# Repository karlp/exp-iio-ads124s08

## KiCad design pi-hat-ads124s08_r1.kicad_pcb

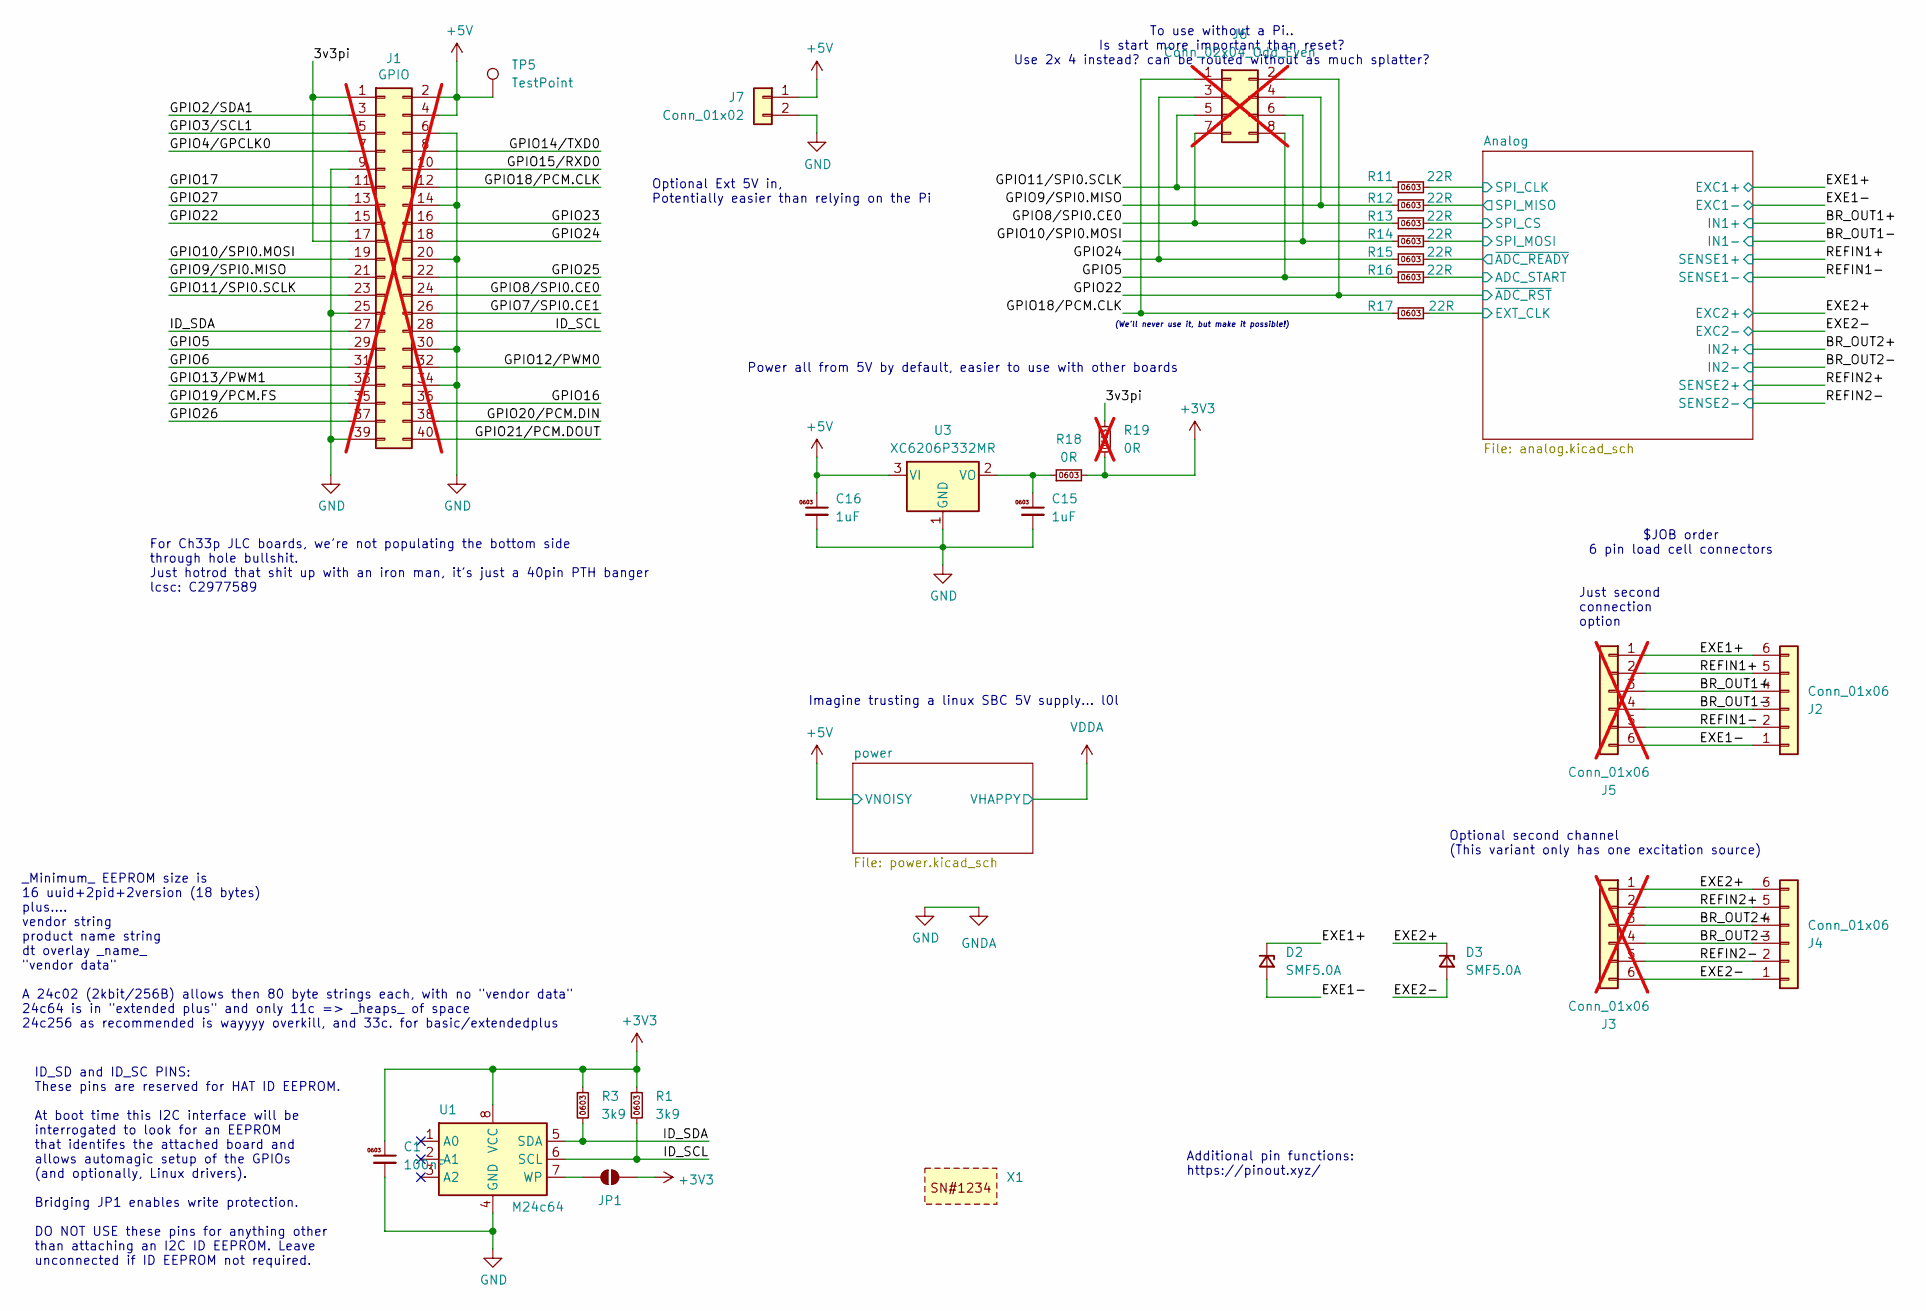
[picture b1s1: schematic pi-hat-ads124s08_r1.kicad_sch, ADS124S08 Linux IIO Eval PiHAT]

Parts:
C1: 100nF; C_0603_1608Metric; MPN CC0603KRX7R9BB104; LCSC Part # C14663
C15, C16: 1uF; C_0603_1608Metric; MPN CL10A105KB8NNNC; LCSC Part # C15849
D2, D3: SMF5.0A; D_SOD-123F; MPN SMF5.0A; LCSC Part # C19077497
J1: GPIO; PinSocket_2x20_P2.54mm_Vertical; not fitted
J2, J4: Conn_01x06; PhoenixContact_MCV_1,5_6-G-3.81_1x06_P3.81mm_Vertical; MPN KF2EDGV-3.81-6P; LCSC Part # C441336
J3, J5: Conn_01x06; PinHeader_1x06_P2.54mm_Vertical; not fitted
J6: Conn_02x04_Odd_Even; PinHeader_2x04_P2.54mm_Vertical; not fitted
J7: Conn_01x02; PhoenixContact_MCV_1,5_2-G-3.81_1x02_P3.81mm_Vertical; MPN WJ15EDGVC-3.81-2P; LCSC Part # C8396
JP1: ID_WP; SolderJumper-2_P1.3mm_Open_TrianglePad0.9x1.8mm
R1, R3: 3k9; R_0603_1608Metric; MPN 0603WAF3901T5E; LCSC Part # C23018
R11, R12, R13, R14, R15, R16, R17: 22R; R_0603_1608Metric; MPN 0603WAF220JT5E; LCSC Part # C23345
R18: 0R; R_0603_1608Metric; MPN 0603WAF0000T5E; LCSC Part # C21189
R19: 0R; R_0603_1608Metric; MPN 0603WAF0000T5E; LCSC Part # C21189; not fitted
TP5: TestPoint; TestPoint_THTPad_2.0x2.0mm_Drill1.0mm
U1: M24c64; SOIC-8_3.9x4.9mm_P1.27mm; MPN M24C64-RMN6TP; LCSC Part # C79988
U3: XC6206P332MR; SOT-23-3; MPN XC6206P332MR-G; LCSC Part # C5446
X1: JLC_2D_BARCODE_8x8mm

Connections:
+3V3: C1.1, JP1.2 (B), R1.1, R3.1, R18.2, R19.1, U1.8 (VCC); also elsewhere on the board
+5V: C16.1, J1.2, J1.4, J7.1, TP5.1, U3.3 (VI); also elsewhere on the board
/3v3pi: J1.1, J1.17, R19.2
/Analog/ADC_START: R16.2; also elsewhere on the board
/Analog/EXT_CLK: R17.2; also elsewhere on the board
/Analog/SPI_CLK: R11.2; also elsewhere on the board
/Analog/SPI_CS: R13.2; also elsewhere on the board
/Analog/SPI_MISO: R12.2; also elsewhere on the board
/Analog/SPI_MOSI: R14.2; also elsewhere on the board
/Analog/~ADC_READY: R15.2; also elsewhere on the board
/BR_OUT1+: J2.4, J5.3; also elsewhere on the board
/BR_OUT1-: J2.3, J5.4; also elsewhere on the board
/BR_OUT2+: J3.3, J4.4; also elsewhere on the board
/BR_OUT2-: J3.4, J4.3; also elsewhere on the board
/EXE1+: D2.1 (K), D3.1 (K), J2.6, J3.1, J4.6, J5.1; also elsewhere on the board
/GPIO2/SDA1: J1.3
/GPIO3/SCL1: J1.5
/GPIO4/GPCLK0: J1.7
/GPIO5: J1.29, J6.8, R16.1
/GPIO6: J1.31
/GPIO7/SPI0.CE1: J1.26
/GPIO8/SPI0.CE0: J1.24, J6.7, R13.1
/GPIO9/SPI0.MISO: J1.21, J6.4, R12.1
/GPIO10/SPI0.MOSI: J1.19, J6.6, R14.1
/GPIO11/SPI0.SCLK: J1.23, J6.5, R11.1
/GPIO12/PWM0: J1.32
/GPIO13/PWM1: J1.33
/GPIO14/TXD0: J1.8
/GPIO15/RXD0: J1.10
/GPIO16: J1.36
/GPIO17: J1.11
/GPIO18/PCM.CLK: J1.12, J6.1, R17.1
/GPIO19/PCM.FS: J1.35
/GPIO20/PCM.DIN: J1.38
/GPIO21/PCM.DOUT: J1.40
/GPIO22: J1.15, J6.2; also elsewhere on the board
/GPIO23: J1.16
/GPIO24: J1.18, J6.3, R15.1
/GPIO25: J1.22
/GPIO26: J1.37
/GPIO27: J1.13
/ID_SCL: J1.28, R1.2, U1.6 (SCL)
/ID_SDA: J1.27, R3.2, U1.5 (SDA)
/REFIN1+: J2.5, J5.2; also elsewhere on the board
/REFIN1-: J2.2, J5.5; also elsewhere on the board
/REFIN2+: J3.2, J4.5; also elsewhere on the board
/REFIN2-: J3.5, J4.2; also elsewhere on the board
GND: C1.2, C15.2, C16.2, D2.2 (A), D3.2 (A), J1.6, J1.9, J1.14, J1.20, J1.25, J1.30, J1.34, J1.39, J2.1, J3.6, J4.1, J5.6, J7.2, U1.4 (GND), U3.1 (GND); also elsewhere on the board
unnamed: JP1.1 (A), U1.7 (WP)
unnamed: C15.1, R18.1, U3.2 (VO)

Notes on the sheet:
Optional Ext 5V in, Potentially easier than relying on the Pi
Just second connection option
_Minimum_ EEPROM size is 16 uuid+2pid+2version (18 bytes) plus.... vendor string product name string dt overlay _name_ "vendor data" A 24c02 (2kbit/256B) allows then 80 byte strings each, with no "vendor data" 24c64 is in "extended plus" and only 11c => _heaps_ of space 24c256 as recommended is way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
To use without a Pi.. Is start more important than reset? Use 2x 4 instead? can be routed without as much splatter?
Additional pin functions: https://pinout.xyz/
$JOB order 6 pin load cell connectors
Power all from 5V by default, easier to use with other boards
ID_SD and ID_SC PINS: These pins are reserved for HAT ID EEPROM. At boot time this I2C interface will be interrogated to look for an EEPROM that identifes the attached board and allows automagic setup of the GPIOs (and optionally, Linux drivers). Bridging JP1 enables write protection. DO NOT USE th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
Optional second channel (This variant only has one excitation source)
For Ch33p JLC boards, we're not populating the bottom side through hole bullshit. Just hotrod that shit up with an iron man, it's just a 40pin PTH banger lcsc: C2977589
(We'll never use it, but make it possible!)
Imagine trusting a linux SBC 5V supply... l0l

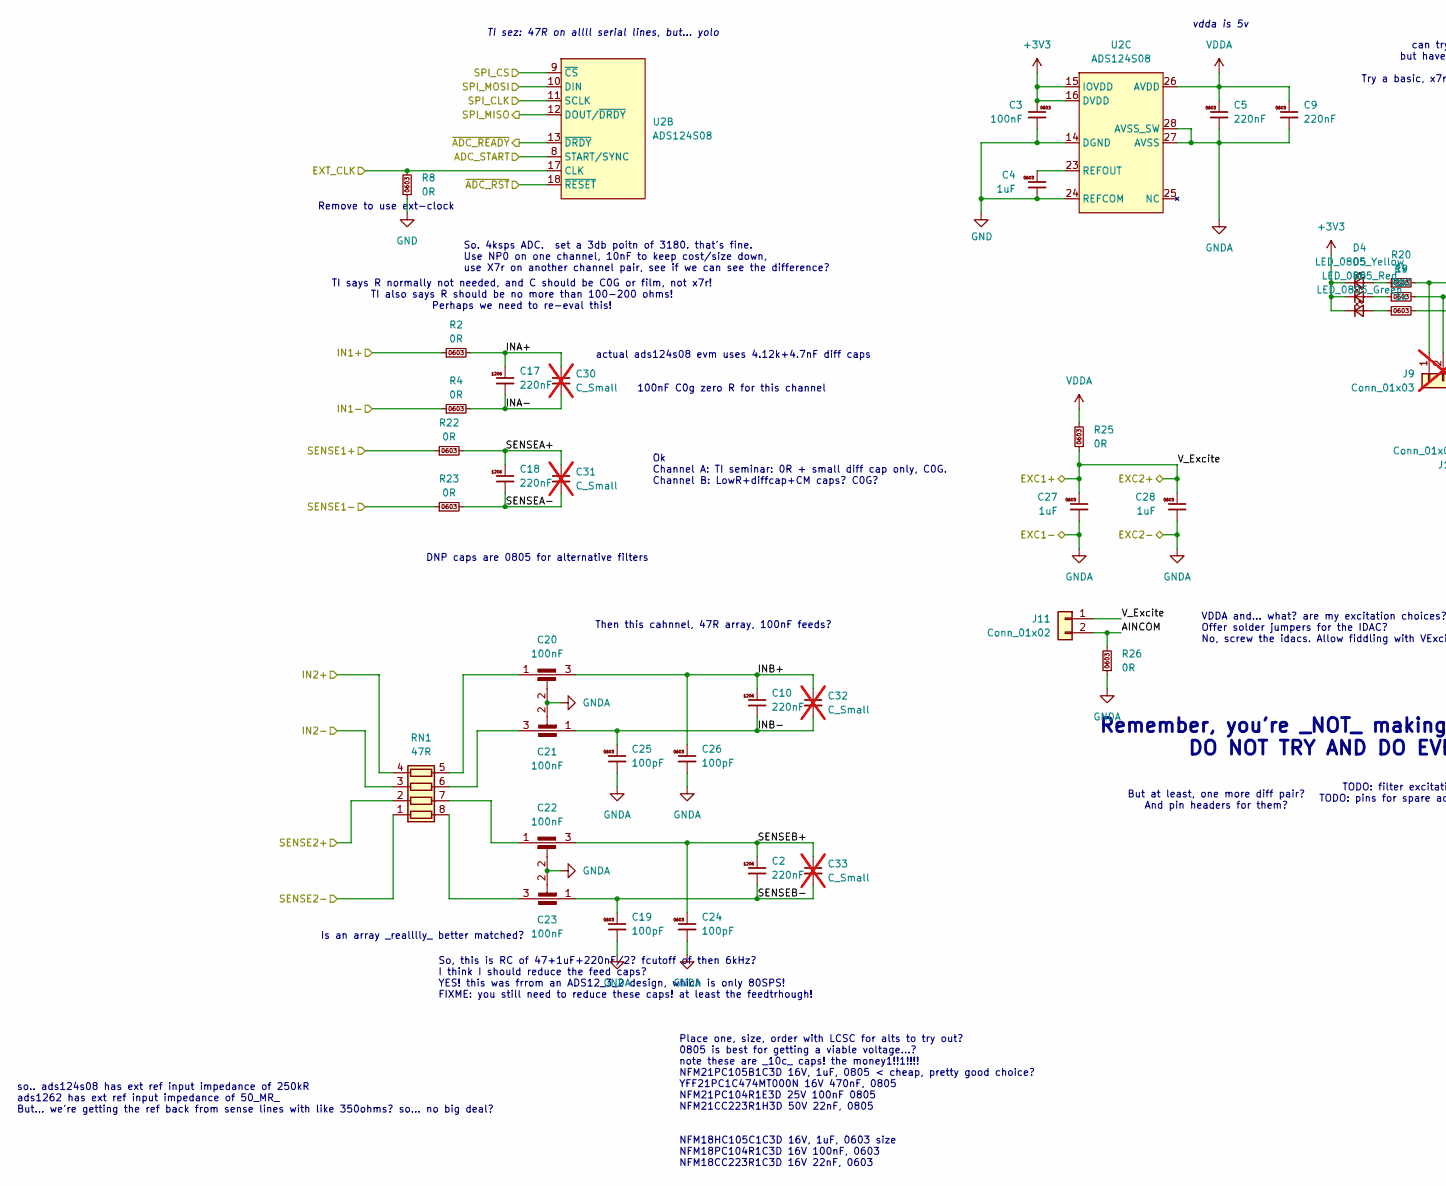
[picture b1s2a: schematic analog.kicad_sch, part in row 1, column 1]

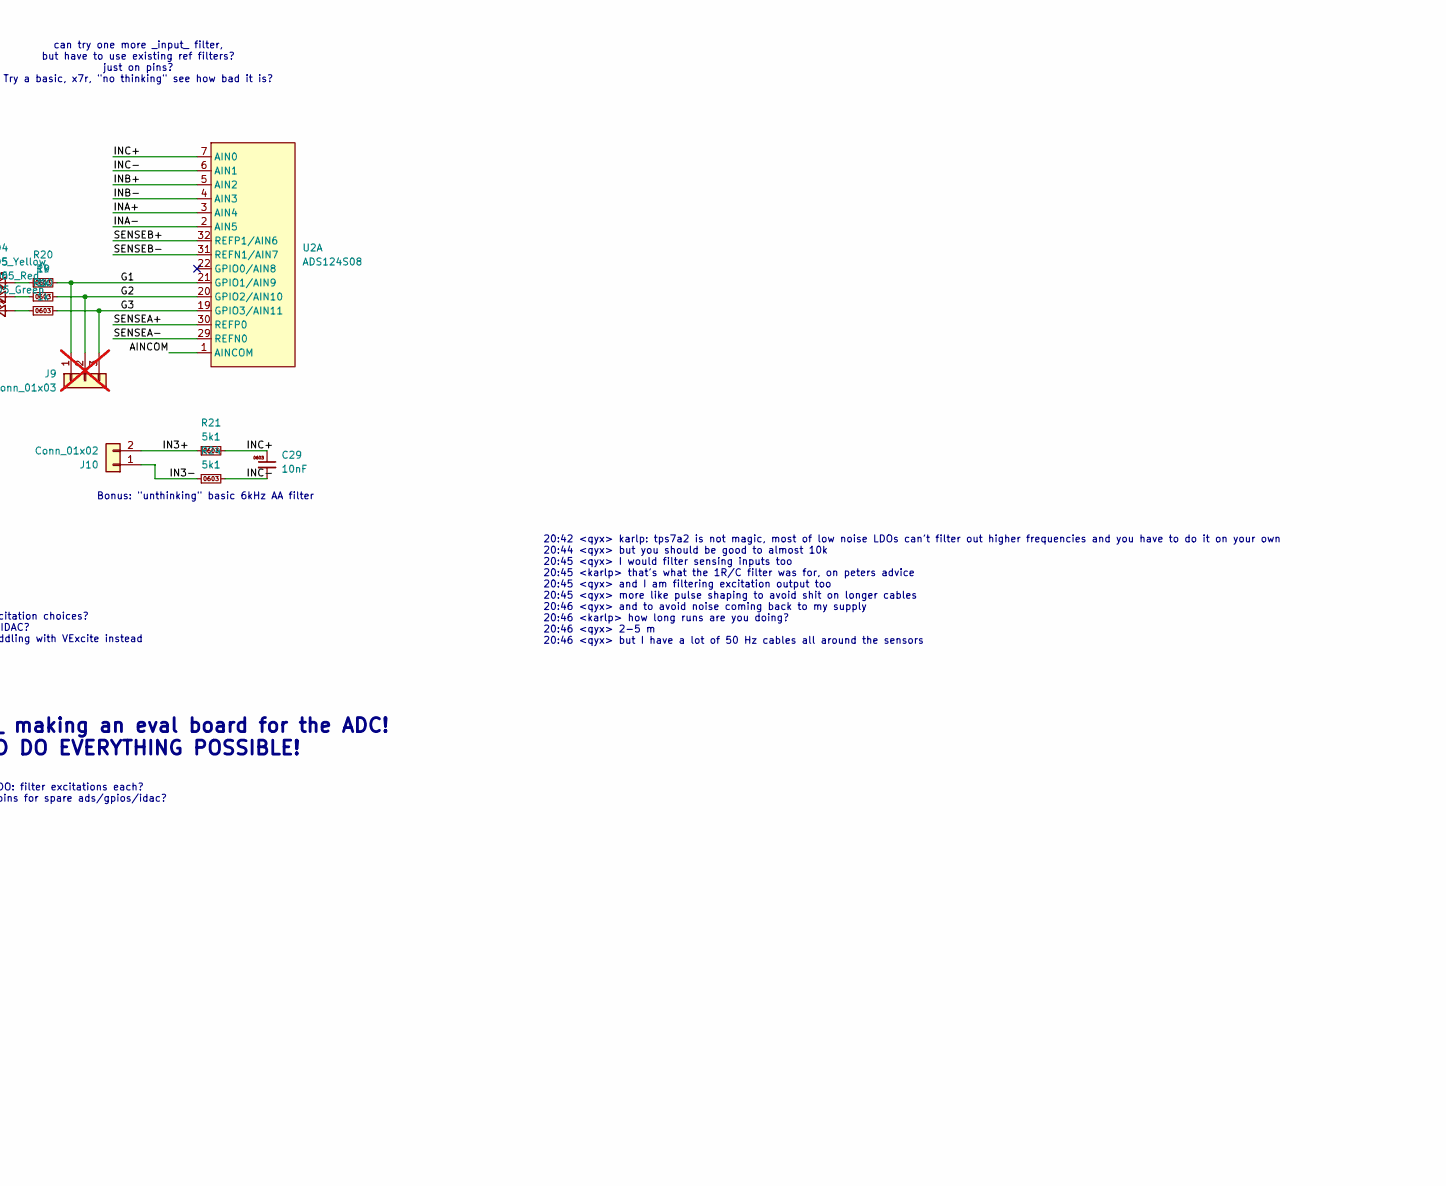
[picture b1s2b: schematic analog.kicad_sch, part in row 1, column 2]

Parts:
C2, C10, C17, C18: 220nF; C_1206_3216Metric; MPN GRM31C5C1H224JE02L; LCSC Part # C464977
C3: 100nF; C_0603_1608Metric; MPN CC0603KRX7R9BB104; LCSC Part # C14663
C4, C27, C28: 1uF; C_0603_1608Metric; MPN CL10A105KB8NNNC; LCSC Part # C15849
C5, C9: 220nF; C_0603_1608Metric; MPN CL10B224KA8NNNC; LCSC Part # C21120
C19, C24, C25, C26: 100pF; C_0603_1608Metric; MPN CL10C101JB8NNNC; LCSC Part # C14858
C20, C21, C22, C23: 100nF; C_Feedthrough_NFM21_2.0mmx1.2mm; MPN NFM21PC104R1E3D; LCSC Part # C86150
C29: 10nF; C_0603_1608Metric; MPN 0603B103K500NT; LCSC Part # C57112
C30, C31, C32, C33: C_Small; C_0805_2012Metric; not fitted
D4: LED_0805_Yellow; LED_0805_2012Metric; MPN KT-0805Y; LCSC Part # C2296
D5: LED_0805_Red; LED_0805_2012Metric; MPN NCD0805R1; LCSC Part # C84256
D6: LED_0805_Green; LED_0805_2012Metric; MPN KT-0805G; LCSC Part # C2297
J9: Conn_01x03; PinHeader_1x03_P2.54mm_Vertical; not fitted
J10, J11: Conn_01x02; PhoenixContact_MCV_1,5_2-G-3.81_1x02_P3.81mm_Vertical; MPN WJ15EDGVC-3.81-2P; LCSC Part # C8396
R2, R4, R8, R22, R23, R25, R26: 0R; R_0603_1608Metric; MPN 0603WAF0000T5E; LCSC Part # C21189
R9, R10, R20: 1k; R_0603_1608Metric; MPN 0603WAF1001T5E; LCSC Part # C21190
R21, R24: 5k1; R_0603_1608Metric; MPN 0603WAF5101T5E; LCSC Part # C23186
RN1: 47R; R_Array_Convex_4x0603; MPN 4D03WGF470JT5E; LCSC Part # C425204
U2: ADS124S08; LQFP-32_5x5mm_P0.5mm; MPN ADS124S08IPBSR; LCSC Part # C2870171

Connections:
+3V3: C3.1, D4.1 (K), D5.1 (K), D6.1 (K), U2.15 (IOVDD), U2.16 (DVDD); also elsewhere on the board
/Analog/ADC_START: U2.8 (START/SYNC); also elsewhere on the board
/Analog/AINCOM: J11.2, R26.2, U2.1 (AINCOM)
/Analog/EXT_CLK: R8.2, U2.17 (CLK); also elsewhere on the board
/Analog/G1: J9.1, R20.2, U2.21 (GPIO1/AIN9)
/Analog/G2: J9.2, R9.2, U2.20 (GPIO2/AIN10)
/Analog/G3: J9.3, R10.2, U2.19 (GPIO3/AIN11)
/Analog/IN3+: J10.2, R21.1
/Analog/IN3-: J10.1, R24.1
/Analog/INA+: C17.1, C30.1, R2.2, U2.3 (AIN4)
/Analog/INA-: C17.2, C30.2, R4.2, U2.2 (AIN5)
/Analog/INB+: C10.1, C20.3, C26.1, C32.1, U2.5 (AIN2)
/Analog/INB-: C10.2, C21.1, C25.1, C32.2, U2.4 (AIN3)
/Analog/INC+: C29.1, R21.2, U2.7 (AIN0)
/Analog/INC-: C29.2, R24.2, U2.6 (AIN1)
/Analog/SENSEA+: C18.1, C31.1, R22.2, U2.30 (REFP0)
/Analog/SENSEA-: C18.2, C31.2, R23.2, U2.29 (REFN0)
/Analog/SENSEB+: C2.1, C22.3, C24.1, C33.1, U2.32 (REFP1/AIN6)
/Analog/SENSEB-: C2.2, C19.1, C23.1, C33.2, U2.31 (REFN1/AIN7)
/Analog/SPI_CLK: U2.11 (SCLK); also elsewhere on the board
/Analog/SPI_CS: U2.9 (~CS); also elsewhere on the board
/Analog/SPI_MISO: U2.12 (DOUT/~DRDY); also elsewhere on the board
/Analog/SPI_MOSI: U2.10 (DIN); also elsewhere on the board
/Analog/~ADC_READY: U2.13 (~DRDY); also elsewhere on the board
/BR_OUT1+: R2.1; also elsewhere on the board
/BR_OUT1-: R4.1; also elsewhere on the board
/BR_OUT2+: RN1.4 (R4.1); also elsewhere on the board
/BR_OUT2-: RN1.3 (R3.1); also elsewhere on the board
/EXE1+: C27.1, C28.1, J11.1, R25.1; also elsewhere on the board
/GPIO22: U2.18 (~RESET); also elsewhere on the board
/REFIN1+: R22.1; also elsewhere on the board
/REFIN1-: R23.1; also elsewhere on the board
/REFIN2+: RN1.2 (R2.1); also elsewhere on the board
/REFIN2-: RN1.1 (R1.1); also elsewhere on the board
GND: C3.2, C4.2, C5.2, C9.2, C19.2, C20.2, C21.2, C22.2, C23.2, C24.2, C25.2, C26.2, C27.2, C28.2, R8.1, R26.1, U2.14 (DGND), U2.24 (REFCOM), U2.27 (AVSS), U2.28 (AVSS_SW); also elsewhere on the board
unnamed: D4.2 (A), R20.1
unnamed: D5.2 (A), R9.1
unnamed: D6.2 (A), R10.1
unnamed: C23.3, RN1.8 (R1.2)
unnamed: C22.1, RN1.7 (R2.2)
unnamed: C21.3, RN1.6 (R3.2)
unnamed: C20.1, RN1.5 (R4.2)
unnamed: C4.1, U2.23 (REFOUT)
VDDA: C5.1, C9.1, R25.2, U2.26 (AVDD); also elsewhere on the board

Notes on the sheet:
DNP caps are 0805 for alternative filters
So, this is RC of 47+1uF+220nF/2? fcutoff of then 6kHz? I think I should reduce the feed caps? YES! this was frrom an ADS12_3_2 design, which is only 80SPS! FIXME: you still need to reduce these caps! at least the feedtrhough!
so.. ads124s08 has ext ref input impedance of 250kR ads1262 has ext ref input impedance of 50_MR_ But... we're getting the ref back from sense lines with like 350ohms? so... no big deal?
Remove to use ext-clock
So. 4ksps ADC. set a 3db poitn of 3180. that's fine. Use NP0 on one channel, 10nF to keep cost/size down, use X7r on another channel pair, see if we can see the difference?
TODO: filter excitations each? TODO: pins for spare ads/gpios/idac?
Place one, size, order with LCSC for alts to try out? 0805 is best for getting a viable voltage...? note these are _10c_ caps! the money1!!1!!!! NFM21PC105B1C3D 16V, 1uF, 0805 < cheap, pretty good choice? YFF21PC1C474MT000N 16V 470nF, 0805 NFM21PC104R1E3D 25V 100nF 0805 NFM21CC223R1H3D 50V 22nF, 08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
Is an array _realllly_ better matched?
VDDA and... what? are my excitation choices? Offer solder jumpers for the IDAC? No, screw the idacs. Allow fiddling with VExcite instead
100nF C0g zero R for this channel
TI sez: 47R on allll serial lines, but... yolo
can try one more _input_ filter, but have to use existing ref filters? just on pins? Try a basic, x7r, "no thinking" see how bad it is?
Bonus: "unthinking" basic 6kHz AA filter
Remember, you're _NOT_ making an eval board for the ADC! DO NOT TRY AND DO EVERYTHING POSSIBLE!
actual ads124s08 evm uses 4.12k+4.7nF diff caps
TI says R normally not needed, and C should be C0G or film, not x7r! TI also says R should be no more than 100-200 ohms! Perhaps we need to re-eval this!
20:42 <qyx> karlp: tps7a2 is not magic, most of low noise LDOs can't filter out higher frequencies and you have to do it on your own 20:44 <qyx> but you should be good to almost 10k 20:45 <qyx> I would filter sensing inputs too 20:45 <karlp> that's what the 1R/C filter was for, on peters advice 20: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
Ok Channel A: TI seminar: 0R + small diff cap only, C0G. Channel B: LowR+diffcap+CM caps? C0G?
But at least, one more diff pair? And pin headers for them?
Then this cahnnel, 47R array, 100nF feeds?
vdda is 5v

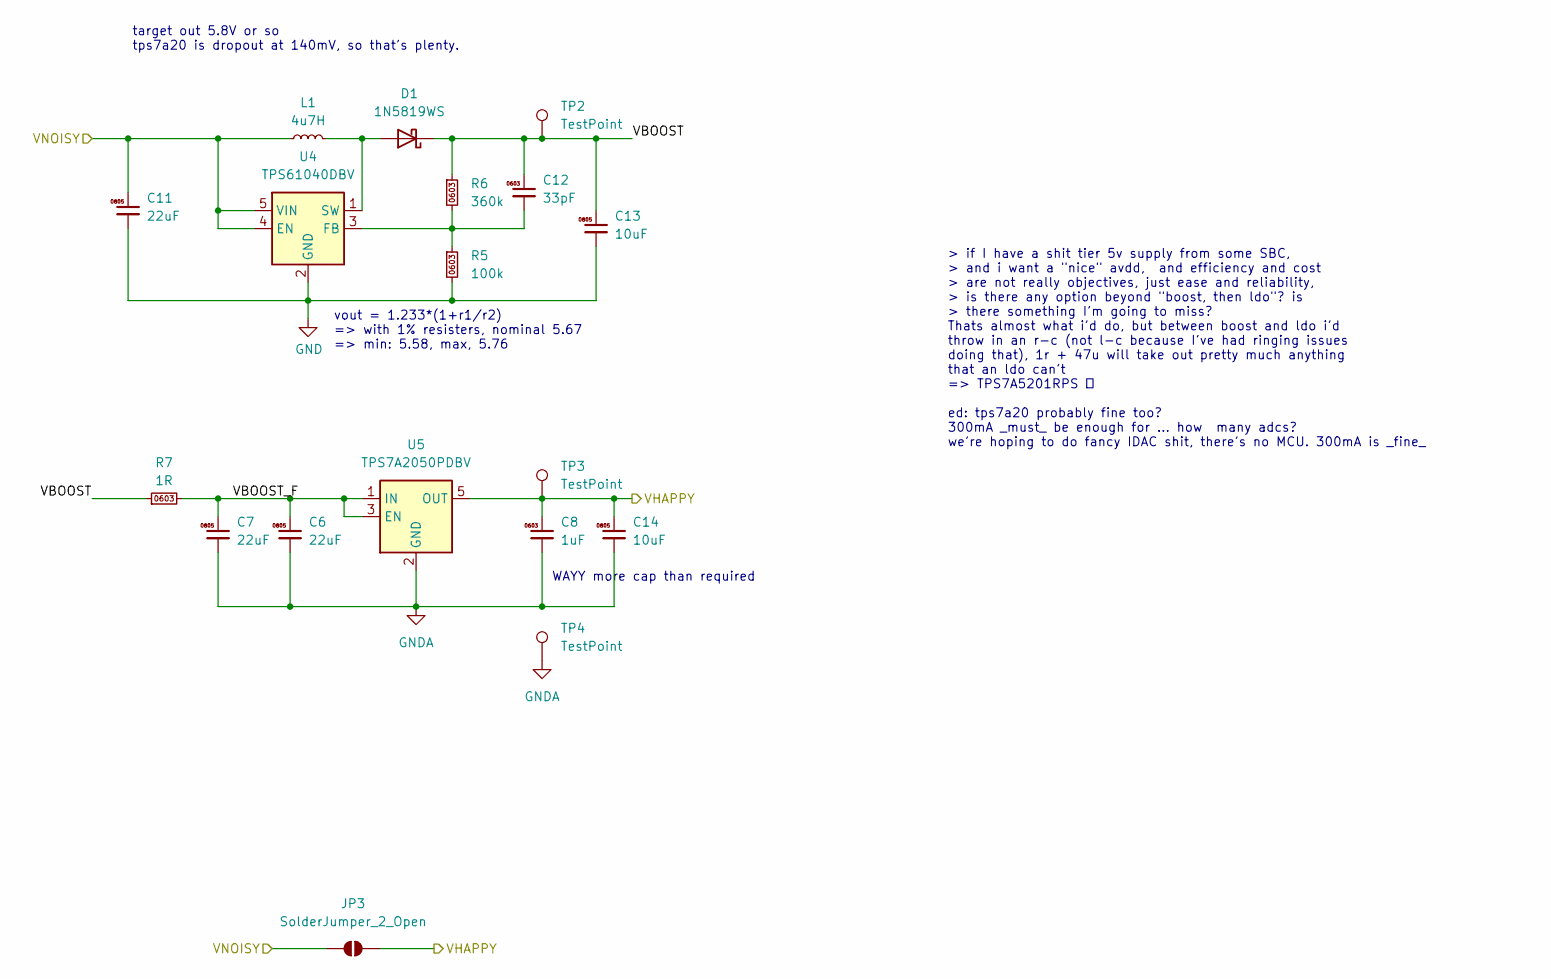
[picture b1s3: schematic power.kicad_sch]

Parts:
C6, C7, C11: 22uF; C_0805_2012Metric; MPN CL21A226MAQNNNE; LCSC Part # C45783
C8: 1uF; C_0603_1608Metric; MPN CL10A105KB8NNNC; LCSC Part # C15849
C12: 33pF; C_0603_1608Metric; MPN CL10C330JB8NNNC; LCSC Part # C1663
C13, C14: 10uF; C_0805_2012Metric; MPN CL21A106KAYNNNE; LCSC Part # C15850
D1: 1N5819WS; D_SOD-323; MPN 1N5819WS; LCSC Part # C191023
JP3: SolderJumper_2_Open; SolderJumper-2_P1.3mm_Open_TrianglePad0.9x1.8mm
L1: 4u7H; L_Changjiang_FNR4030S; MPN FNR4030S4R7MT; LCSC Part # C167874
R5: 100k; R_0603_1608Metric; MPN 0603WAF1003T5E; LCSC Part # C25803
R6: 360k; R_0603_1608Metric; MPN 0603WAF3603T5E; LCSC Part # C23146
R7: 1R; R_0603_1608Metric; MPN 0603WAF100KT5E; LCSC Part # C22936
TP2, TP3, TP4: TestPoint; TestPoint_THTPad_2.0x2.0mm_Drill1.0mm
U4: TPS61040DBV; SOT-23-5; MPN TPS61040DBVR; LCSC Part # C7722
U5: TPS7A2050PDBV; SOT-23-5; MPN TPS7A2050PDBVR; LCSC Part # C2864504

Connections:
+5V: C11.1, JP3.1 (A), L1.1, U4.4 (EN), U4.5 (VIN); also elsewhere on the board
/power/VBOOST: C12.1, C13.1, D1.1 (K), R6.1, R7.1, TP2.1
/power/VBOOST_F: C6.1, C7.1, R7.2, U5.1 (IN), U5.3 (EN)
GND: C6.2, C7.2, C8.2, C11.2, C13.2, C14.2, R5.2, TP4.1, U4.2 (GND), U5.2 (GND); also elsewhere on the board
unnamed: D1.2 (A), L1.2, U4.1 (SW)
unnamed: C12.2, R5.1, R6.2, U4.3 (FB)
VDDA: C8.1, C14.1, JP3.2 (B), TP3.1, U5.5 (OUT); also elsewhere on the board

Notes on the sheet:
> if I have a shit tier 5v supply from some SBC, > and i want a "nice" avdd, and efficiency and cost > are not really objectives, just ease and reliability, > is there any option beyond "boost, then ldo"? is > there something I'm going to miss? Thats almost what i'd do, but between boost and ldo i'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
vout = 1.233*(1+r1/r2) => with 1% resisters, nominal 5.67 => min: 5.58, max, 5.76
target out 5.8V or so tps7a20 is dropout at 140mV, so that's plenty.
WAYY more cap than required

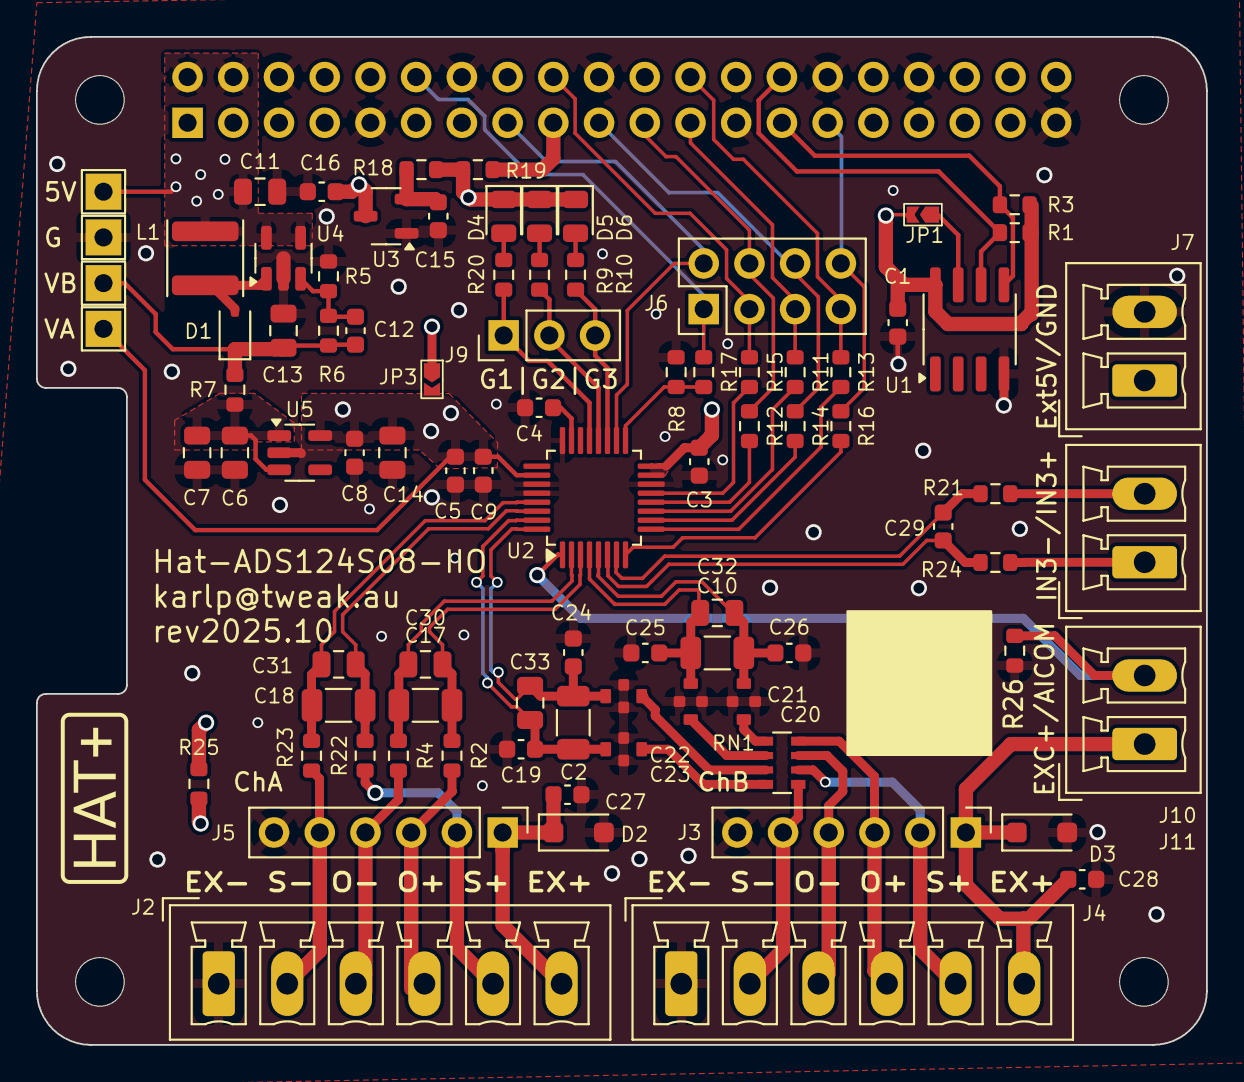
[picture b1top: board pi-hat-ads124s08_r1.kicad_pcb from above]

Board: 4 copper layers, 65.0 x 56.0 mm, 93 parts (1 on the bottom side), 61 nets.

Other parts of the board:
MH1, MH2, MH3, MH4: MountingHole_2.7mm_M2.5

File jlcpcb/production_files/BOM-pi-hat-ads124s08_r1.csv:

Comment,Designator,Footprint,LCSC,Quantity
100nF,"C1,C3",C_0603_1608Metric,C14663,2
100pF,"C19,C24,C25,C26",C_0603_1608Metric,C14858,4
1uF,"C15,C16,C27,C28,C4,C8",C_0603_1608Metric,C15849,6
10uF,"C13,C14",C_0805_2012Metric,C15850,2
33pF,C12,C_0603_1608Metric,C1663,1
4u7H,L1,L_Changjiang_FNR4030S,C167874,1
SMF5.0A,"D2,D3",D_SOD-123F,C19077497,2
1N5819WS,D1,D_SOD-323,C191023,1
220nF,"C5,C9",C_0603_1608Metric,C21120,2
0R,"R18,R2,R22,R23,R25,R26,R4,R8",R_0603_1608Metric,C21189,8
1k,"R10,R20,R9",R_0603_1608Metric,C21190,3
1R,R7,R_0603_1608Metric,C22936,1
LED_0805_Yellow,D4,LED_0805_2012Metric,C2296,1
LED_0805_Green,D6,LED_0805_2012Metric,C2297,1
3k9,"R1,R3",R_0603_1608Metric,C23018,2
360k,R6,R_0603_1608Metric,C23146,1
5k1,"R21,R24",R_0603_1608Metric,C23186,2
22R,"R11,R12,R13,R14,R15,R16,R17",R_0603_1608Metric,C23345,7
100k,R5,R_0603_1608Metric,C25803,1
TPS7A2050PDBV,U5,SOT-23-5,C2864504,1
ADS124S08,U2,LQFP-32_5x5mm_P0.5mm,C2870171,1
47R,RN1,R_Array_Convex_4x0603,C425204,1
Conn_01x06,"J2,J4","PhoenixContact_MCV_1,5_6-G-3.81_1x06_P3.81mm_Vertical",C441336,2
22uF,"C11,C6,C7",C_0805_2012Metric,C45783,3
220nF,"C10,C17,C18,C2",C_1206_3216Metric,C464977,4
XC6206P332MR,U3,SOT-23-3,C5446,1
10nF,C29,C_0603_1608Metric,C57112,1
TPS61040DBV,U4,SOT-23-5,C7722,1
M24c64,U1,SOIC-8_3.9x4.9mm_P1.27mm,C79988,1
Conn_01x02,"J10,J11,J7","PhoenixContact_MCV_1,5_2-G-3.81_1x02_P3.81mm_Vertical",C8396,3
LED_0805_Red,D5,LED_0805_2012Metric,C84256,1
100nF,"C20,C21,C22,C23",C_Feedthrough_NFM21_2.0mmx1.2mm,C86150,4
TestPoint,TP2,TestPoint_THTPad_2.0x2.0mm_Drill1.0mm,,1
Conn_01x06,,PinHeader_1x06_P2.54mm_Vertical,,0
TestPoint,TP3,TestPoint_THTPad_2.0x2.0mm_Drill1.0mm,,1
Conn_01x06,,PinHeader_1x06_P2.54mm_Vertical,,0
TestPoint,TP4,TestPoint_THTPad_2.0x2.0mm_Drill1.0mm,,1
~,X1,JLC_2D_BARCODE_8x8mm,,1
Conn_02x04_Odd_Even,,PinHeader_2x04_P2.54mm_Vertical,,0
Conn_01x03,,PinHeader_1x03_P2.54mm_Vertical,,0
TestPoint,TP5,TestPoint_THTPad_2.0x2.0mm_Drill1.0mm,,1
ID_WP,JP1,SolderJumper-2_P1.3mm_Open_TrianglePad0.9x1.8mm,,1
GPIO,,PinSocket_2x20_P2.54mm_Vertical,,0
C_Small,,C_0805_2012Metric,,0
C_Small,,C_0805_2012Metric,,0
C_Small,,C_0805_2012Metric,,0
C_Small,,C_0805_2012Metric,,0

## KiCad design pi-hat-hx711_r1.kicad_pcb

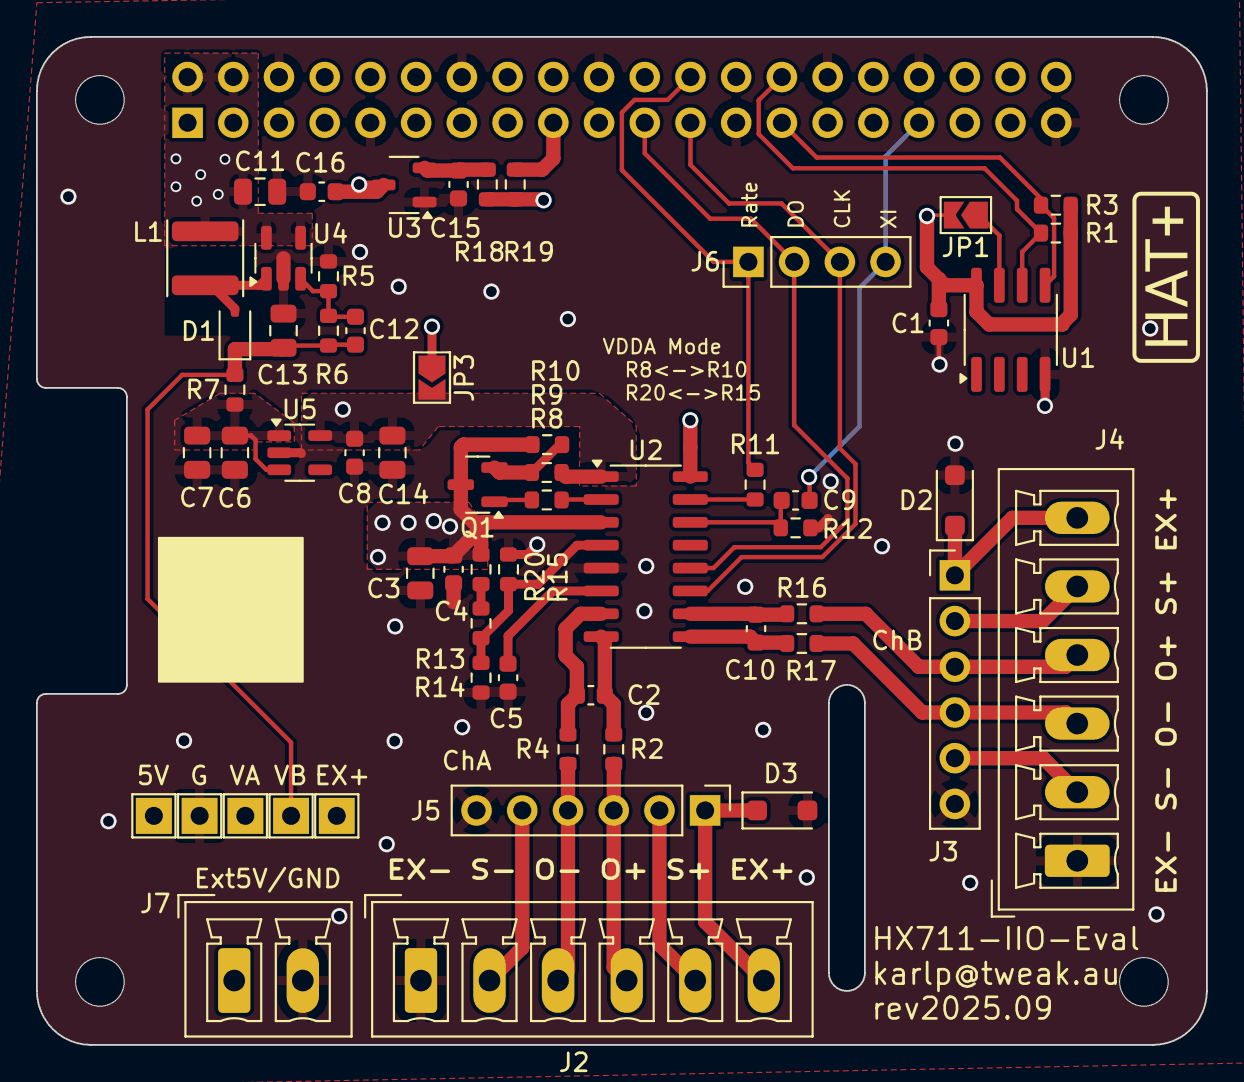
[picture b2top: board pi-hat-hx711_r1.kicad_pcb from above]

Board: 4 copper layers, 65.0 x 56.0 mm, 65 parts (1 on the bottom side), 38 nets.

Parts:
C1, C2, C4, C5, C10: 100nF; C_0603_1608Metric
C3, C13, C14: 10uF; C_0805_2012Metric
C6, C7, C11: 22uF; C_0805_2012Metric
C8, C15, C16: 1uF; C_0603_1608Metric
C9, C12: 33pF; C_0603_1608Metric
D1: 1N5819WS; D_SOD-323
D2, D3: SMF5.0A; D_SOD-123F
J1: GPIO; PinSocket_2x20_P2.54mm_Vertical
J2, J4: Conn_01x06; PhoenixContact_MCV_1,5_6-G-3.81_1x06_P3.81mm_Vertical
J3, J5: Conn_01x06; PinHeader_1x06_P2.54mm_Vertical
J6: Conn_01x04; PinHeader_1x04_P2.54mm_Vertical
J7: Conn_01x02; PhoenixContact_MCV_1,5_2-G-3.81_1x02_P3.81mm_Vertical
JP1: ID_WP; SolderJumper-2_P1.3mm_Open_TrianglePad1.0x1.5mm
JP3: SolderJumper_2_Open; SolderJumper-2_P1.3mm_Open_TrianglePad1.0x1.5mm
L1: 4u7H; L_Changjiang_FNR4030S
MH1, MH2, MH3, MH4: MountingHole_2.7mm_M2.5
Q1: S8550; SOT-23
R1, R3, R14: 3k9; R_0603_1608Metric
R2, R4, R16, R17: 100R; R_0603_1608Metric
R5: 100k; R_0603_1608Metric
R6: 360k; R_0603_1608Metric
R7: 1R; R_0603_1608Metric
R8, R9, R10, R12, R15, R18, R19, R20: 0R; R_0603_1608Metric
R11, R13: 10k; R_0603_1608Metric
TP1, TP2, TP3, TP4, TP5: TestPoint; TestPoint_THTPad_2.0x2.0mm_Drill1.0mm
U1: M24c64; SOIC-8_3.9x4.9mm_P1.27mm
U2: HX711; SOIC-16_3.9x9.9mm_P1.27mm
U3: XC6206P332MR; SOT-23-3
U4: TPS61040DBV; SOT-23-5
U5: TPS7A2050PDBV; SOT-23-5
X1: JLC_2D_BARCODE_8x8mm

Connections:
+3V3: C1.1, JP1.2 (B), R1.1, R3.1, R18.2, R19.1, U1.8 (VCC), U2.16 (DVDD)
+5V: C11.1, C16.1, J1.2, J1.4, J7.1, JP3.1 (A), L1.1, TP5.1, U3.3 (VI), U4.4 (EN), U4.5 (VIN)
/3v3pi: J1.1, J1.17, R19.2
/Analog/IN1+: C2.1, R2.1, U2.8 (INA+)
/Analog/IN1-: C2.2, R4.1, U2.7 (INA-)
/Analog/INB+: C10.1, R16.1, U2.10 (INB+)
/Analog/INB-: C10.2, R17.1, U2.9 (INB-)
/BR_OUT1+: J2.4, J5.3, R2.2
/BR_OUT1-: J2.3, J5.4, R4.2
/BR_OUT2+: J3.3, J4.4, R16.2
/BR_OUT2-: J3.4, J4.3, R17.2
/EXE1+: C3.1, C4.1, D2.1 (K), D3.1 (K), J2.6, J3.1, J4.6, J5.1, Q1.3 (C), R10.1, R20.2, TP1.1, U2.3 (AVDD)
/GPIO8/SPI0.CE0: J1.24, J6.1, R11.2
/GPIO9/SPI0.MISO: J1.21, J6.2, U2.12 (DOUT)
/GPIO11/SPI0.SCLK: J1.23, J6.3, U2.11 (PD_SCK)
/GPIO13/PWM1: C9.2, J1.33, J6.4
/ID_SCL: J1.28, R1.2, U1.6 (SCL)
/ID_SDA: J1.27, R3.2, U1.5 (SDA)
/REFIN1+: J2.5, J5.2
/REFIN1-: J2.2, J5.5
/REFIN2+: J3.2, J4.5
/REFIN2-: J3.5, J4.2
/power/VBOOST: C12.1, C13.1, D1.1 (K), R6.1, R7.1, TP2.1
/power/VBOOST_F: C6.1, C7.1, R7.2, U5.1 (IN), U5.3 (EN)
GND: C1.2, C3.2, C4.2, C5.2, C6.2, C7.2, C8.2, C11.2, C13.2, C14.2, C15.2, C16.2, D2.2 (A), D3.2 (A), J1.6, J1.9, J1.14, J1.20, J1.25, J1.30, J1.34, J1.39, J2.1, J3.6, J4.1, J5.6, J7.2, R5.2, R12.1, R14.2, R15.1, TP4.1, U1.4 (GND), U2.5 (AGND), U3.1 (GND), U4.2 (GND), U5.2 (GND)
unnamed: D1.2 (A), L1.2, U4.1 (SW)
unnamed: JP1.1 (A), U1.7 (WP)
unnamed: Q1.1 (B), R8.1
unnamed: Q1.2 (E), R9.1, R10.2
unnamed: R13.1, R20.1
unnamed: R8.2, U2.2 (BASE)
unnamed: R11.1, U2.15 (RATE)
unnamed: C5.1, U2.6 (VBG)
unnamed: R13.2, R14.1, R15.2, U2.4 (VFB)
unnamed: C9.1, R12.2, U2.14 (XI)
unnamed: C15.1, R18.1, U3.2 (VO)
unnamed: C12.2, R5.1, R6.2, U4.3 (FB)
VDDA: C8.1, C14.1, JP3.2 (B), R9.2, TP3.1, U2.1 (VSUP), U5.5 (OUT)

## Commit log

2025-08-30 initial save
2025-08-30 loloxoxlxoxl
2025-08-30 lollll
2025-08-30 continuing.
    might as well have channel b be usable for sense.
    provide options for bypassing power shits though.
    still ratiometric, just avoiding whatever is in the hx711 itself.
2025-08-30 add the sheets that we refactored too...
2025-08-30 just pretty-fying
2025-08-30 rough blocking out the pcb
2025-09-01 better parts, start pushing layout blocks
    SMA is dumb, way too big
    the swpa3030 was... unnecessarily small. we're trying to be super chill
    power here, don't push it hot. (Still, 1A was.. really, more than
    enough? but 1A is a 40C rise, so.. let's just have less....)
    use more caps too. why the fuck not. more filtering, more happy.
    holy fuck though, kicad on wayland is giving me the shits!
2025-09-01 add second channel input
    switch to vertical connectors, so no concerns abotu edge space.
    Allows offering the second channel, even though it's probably useless,
    but it sets us up with a style we might be ok with for subsequent
    boards.
2025-09-01 pushing blocks
    roughyl how we want it?
2025-09-02 chunk out routing
    looks okish?
    switched x2son for plain sot235, it's better stocked at jlc anyway, and
    easier to probe and work with.
2025-09-02 pushing silk, are we done?!
2025-09-04 wheeww!
    Added 3.3v supply from 5V by default.
    Added header to access IOs without rpi
    Added TP to supply/monitor raw 5V (use without pi)
    Adjusted TPs to be on 2.54mm spacing to get headers if desired
    Added TVS on EXE+ lines.
2025-09-04 erc/drc cleanups
    fix lots of off grid stuff that got dragged off in earlier
    re-arrangements
2025-09-04 adds a 2 pin power in connector
    I don't have any suitable power supplies for RPi, so just put on a
    connector to use external if desired. Totally raw unprotected, just
    feeds straight to the rpi.
2025-10-06 initial cut.
    power and serial interface first cut complete...
2025-10-07 blocking out...
2025-10-08 progressing, blocking things out, pondering orbz
2025-10-08 notes and tweaks.
    notes on inputs, filter ref, spi series R.
2025-10-09 overhausl inputs a lot
    read too much, thought too much.
    try one with the "just 0R plus a nice big good quality cap" from the TI
    precision seminar, describing common realities, as well as mixing in
    what they did on the ads1262ref scale design document for the second
    channel with a more "full blown" input filter.
    I don't really like how none of this seems to be a proper AA filter,
2025-10-09 thanks, I hate it.
2025-10-13 moarh updates
    we commit to save our progress
2025-10-14 "ready" ?
    Added 0805 footprints for the diff caps, to try different values there.
    for the smaller nF values, 080 is _way_ cheaper than the 1206 that's
    ~required for the big nF values.
    Pushed a lot of silk....
2025-10-15 "final" to order
    added a jumper for aincom to ground.
2025-10-15 Saving what was ordered.
    $12 PCBs, $70 parts and assembly for 5. not bad.
